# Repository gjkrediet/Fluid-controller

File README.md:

# Fluid-controller
A wireless battery powered pendant for FluidNC based on esp32

This controller uses bluetooth for communication. Be aware that bluetooth and wifi can not be used at the same time and, in fact, need different fluid-nc firmwares.  Sardar Azari seems to have adapted the controller to communicate via tcp. Take a look at https://github.com/AC8L/FluidNC-Pendant

# Main functions
Display shows: 
Machine coördinates, Work coördinates, Spindle speed and state, Set speed and step size when using joystick and rotation encoder, Overrides (Speed, Feed, Rapid),	Machine state, Battery state, Current buttons functions

Main functions buttons, joystick and dial: 
Wake up, Jog gantry and spindle via joystick and/or dial, Set Jog step size and speed via dial, Set spindle speed and switch on/off,	Set overrides (Speed, Feed, Rapid),	Cancel/abort job.

Main functions menu: 
Home machine, Zero workcoördinates, Go to zero, Probe.

# Hardware
1. LilyGO TTGO T-Display V1.1 which is a developmentboard with an ESP32, with a built-in tft (IPS) display and battery-charger. I purchased it for about €13 from internet.
2. Rotary encoder / dial (about €1)
3. Three colored buttons NO (total of €2)
4. PSP joystick (about €3)
5. Lion 18650 battery (€7)
6. Single-sided pcb
7. some pieces of wire (preferably different colors) of which five have female dupont-connectors
8. PLA (25 meter)
9. 8 screws M3 x 8

# Schematic and PCB

The pcb only holds the TTGO developmentboard and the rotary-encoder. The other components are mounted on the lid and wired to the pcb. The schematic of the pcb (in Kicad) is therefore very simple. The isolation-routing of the PCB was done with the very same CNC-router I made this controller for. To fit in the joystick, a corner of the PCB had to be sawed of (Later I updated the edge-cuts in Kicad so now the design should be OK).

The three buttons are at one side connected to the ground (all to J1.1) and are connected tot J1.2, J1.3 and J1.4 respectively.
The joystick is connected tot J2 with J2.2 unconnected (Because I later decided to wire the VCC of the joystick to an output-pin).

# Programming

Programming is done in Arduino IDE. All code exists in one single file. Most constants are enumerated or set with defines at the beginning. I hope it will explain itself to some extent.

Compile with partition scheme minimal SPIFFS or it will not fit.

# Case

# Assembly

Schematic drawing of the lid with positioning of the components (excl. battery).

Female headers and the rotary encoder are soldered on the pcb. The other components are connected to the PCB with wires. Plus and minus wires are directly soldered to the battery and connected to the TTGO with a JST-connector.

To further reduce the powerconsumption I decided to feed the joystick via an outputpin of the esp32, which is why you see the red wire soldered on later.

The battery is wired to the JST-connector on the TTGO

# How to operate

The functions of the pendant were tailored to my needs. Below an oversight of the functions of the various buttons and button-combinations and the menu-options. It might be somewhat cryptic but I hope it may help.

JS=Joystick, BD=dial, BR=red button, BG=green button, BY=yellow button

Switch the pendant on: press JS

Reset the pendant: press JS

The pendant powers off after some time when idle or via the appropriate menu-option.

The pendant can either be in home-state (PH) or menu-state (PM).

Function of the dial-knob can be changed by rotating the dial while pressing BG.

Functions can be (default is DJ; function is indicated on the display with a blue circle):
- DX: Jog 1 step X-axis
- DY: Jog 1 step Y-axis
-	DZ: Jog 1 step Z-axis
-	DS: Set spindle-speed
-	DJ: set jogspeed and step-size
-	DOF: set override Feed
-	DOS: set override Speed
-	DOR: set override Rapid

The function of the buttons depend on the machine-state (MS, shown in the middle of the display of the pendant; function of BR, BG, BY shown on the bottom line of the display). They are as follows.

PH:
  -	JS + MS=Idle or MS=Jog:
    -	Up/down: jog Y-axis
    -	Left/Right: jog X-axis
  -	JS + MS=Idle or MS=Jog + BR (keep pressed)
    -	Up/down: jog Z-axis
    -	Left/Right: no function
  -	BG: enter PM
  -	BY: abort machine-operation
  -	BG (keep pressed) + BD: Change function dial-knob
  -	BR + MS=Alarm: Unlock Machine
  -	BR + DS: Spindle on/off

PM:
  -	BD: navigate menu (poweroff, spindlespeed, spindle on/off, small/large steps for changing jogspeed/stepsize, exit menu, home the machine, Set current Work XY-position to zero, Set current Work Z-position to zero, Probe Z-axis, Jog machine to XY-position zero, unlock Machine (grbl), reset Machine (grbl), Set and save brightness).
  -	BG: confirm menu-choice
  -	BR: Cancel
  -	BR (long press): poweroff

## OTA
Powering on the pendant while keeping the the red button pressed will start Wifi and activate OTA (Over The Air programming from within the Arduino IDE).

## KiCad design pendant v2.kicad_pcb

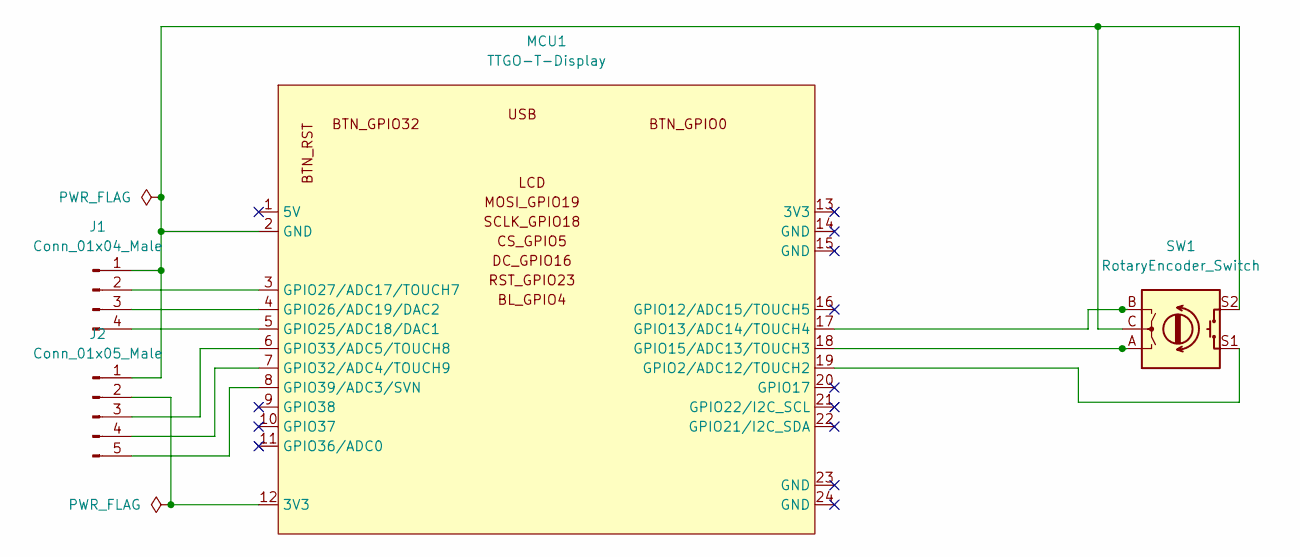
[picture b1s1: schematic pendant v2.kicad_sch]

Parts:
J1: Conn_01x04_Male; PinHeader_1x04_P2.54mm_Vertical
J2: Conn_01x05_Male; PinHeader_1x05_P2.54mm_Vertical
MCU1: TTGO-T-Display
SW1: RotaryEncoder_Switch; RotaryEncoder_Alps_EC12E-Switch_Vertical_H20mm

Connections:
unnamed: J1.1, J2.1, MCU1.2 (GND), SW1.C, SW1.S2
unnamed: J1.2, MCU1.3 (GPIO27/ADC17/TOUCH7)
unnamed: J1.3, MCU1.4 (GPIO26/ADC19/DAC2)
unnamed: J1.4, MCU1.5 (GPIO25/ADC18/DAC1)
unnamed: J2.3, MCU1.6 (GPIO33/ADC5/TOUCH8)
unnamed: J2.4, MCU1.7 (GPIO32/ADC4/TOUCH9)
unnamed: J2.5, MCU1.8 (GPIO39/ADC3/SVN)
unnamed: J2.2, MCU1.12 (3V3)
unnamed: MCU1.17 (GPIO13/ADC14/TOUCH4), SW1.B
unnamed: MCU1.18 (GPIO15/ADC13/TOUCH3), SW1.A
unnamed: MCU1.19 (GPIO2/ADC12/TOUCH2), SW1.S1

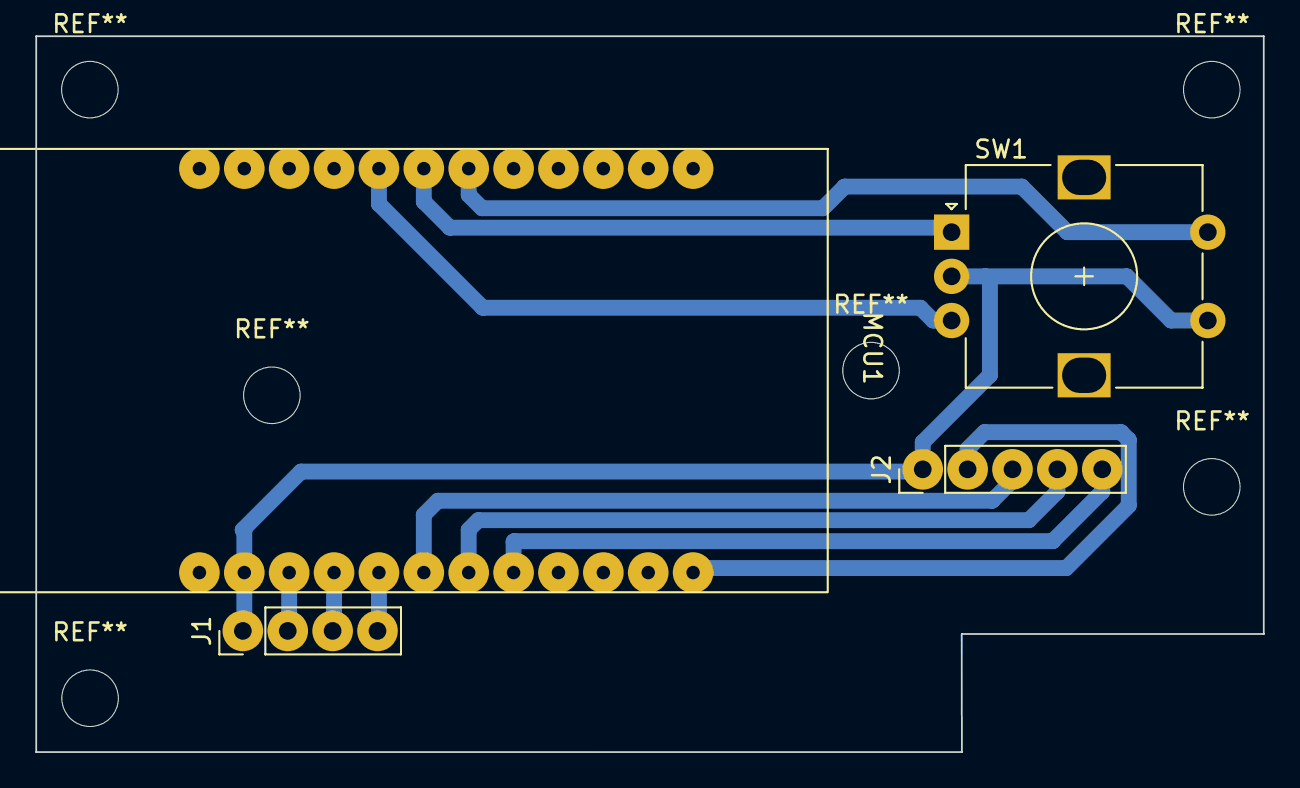
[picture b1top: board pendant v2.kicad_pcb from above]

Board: 2 copper layers, 69.5 x 40.5 mm, 4 parts (0 on the bottom side), 11 nets.

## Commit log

2023-01-25 Add files via upload
    Pictures, STL-files and the scad-files.
    # scad
    The scad-file was made 'quick and dirty'. Be carefull when you change anything.
    # printing
    I printed this in PLA. The case with the smaller bottom flat on the bed and no support.
2023-10-21 Update README.md
    Added hardware for wiring
2023-10-23 updated the edge-cuts to make room for the joystick module
2026-05-03 Fix typos and improve clarity in README.md
